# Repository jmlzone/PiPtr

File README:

This is the README for the Rasberry Pi Ham Hadio Repeater Controller
project.  The Goal of this project is to develop an inexpensive
linking repeater controller witha cost of aproximatly $100/port vs
current commerical solutions which are closer to $160/port.

This is an extensable linkable controller with both local and remote
linking.

For information on the mmra network see mmra.org
For information on this project contact jml@jmlzone.com.

For information on setting up this project on a Pi3 please see the Quickstart.txt

Most of the code will be in Python, however some of it is in C.

Eventually there will be good documeation and a bug/enhancement
tracking WIKI or some such thing.

Current state: The test repeater is stable on the air but many many
things are still to be done.

----------------------------------------------------------------------
Mailing lists for the project
  Please join one or more of the groups below.
MMRA-PiPtr-Hardware+subscribe@groups.io
MMRA-PiPtr-Software+subscribe@groups.io
MMRA-PiPtr-Documentation+subscribe@groups.io

----------------------------------------------------------------------

As you know the MMRA maintains a network of 22 repeaters.  A repeater
is basically a receiver, a transmitter and a controller
in-between. While the network generally works, there are some upgrades
we are continually working on.  One of these efforts being led by me,
James N1DDK, is developing a new repeater controller to enhance the
remote controllability, monitoring and adjusting of the
repeaters. Most of the repeater controller in use today are based on
designs over 20 years old. There have been many advances in technology
in the past 20 years. This project is bringing a more modern, more
scalable and more software based and controllable approach based on
mostly standard hardware and using popular modern methods.

 There are some guiding principles to this project:
1) No Jumpers, switches or mechanical pots that can be set incorectly at a site needing a return visit.
2) Open source -- its part of the Ham culture to experiment and share. This will also ensure longevity of the project beyond the initial developers.
3) Better ease of use than similar commercial products.
4) Scaleability and cost per port more effective than the commercial products.
5) Mostly software for simple functions like CTCSS encode / decode, DTMF encode / decode, timers, morse etc.
6) Well documented

Goals
 * Ease of use for users and control operators.
 * Web back end to view status and control linking.
 * Ability to sell hardware as a fundraiser for MMRA.

To this end I have been working mostly solo with some input from K1IW and W1BRI (and some non members) and I have a working prototype on the air on 224.080 as part of a test platform. The next goals will be to make some boards and have further testing and development.

Here is a list of some of the help that is desired:
 * Programming help in C and Python (possibly java/java script for some of the web interface)
 * Schematics design/review for the custom audio board.
 * Documentation help -- there is some basic documentation, but it would be good to have much more on both hardware, software and user guides.
 * Mechanical/sheet metal design for an enclosure, etc
 * Building help, both mechanical and building the initial boards for testing.
 * Testing help using the controller on a bench and trying things before we put them on the air.
 * On the air testing.

Want to learn more?
 There is a git-hub repository for the software, documentation and issue tracking:
https://github.com/jmlzone/PiPtr
There may be a talk about the project at Boxborough!

Even if you don't know anything about software or repeater controllers you can still help! You don't need to know anything to be a documentation volunteer!

Ready to help?
Contact James, n1ddk@mmra.org.

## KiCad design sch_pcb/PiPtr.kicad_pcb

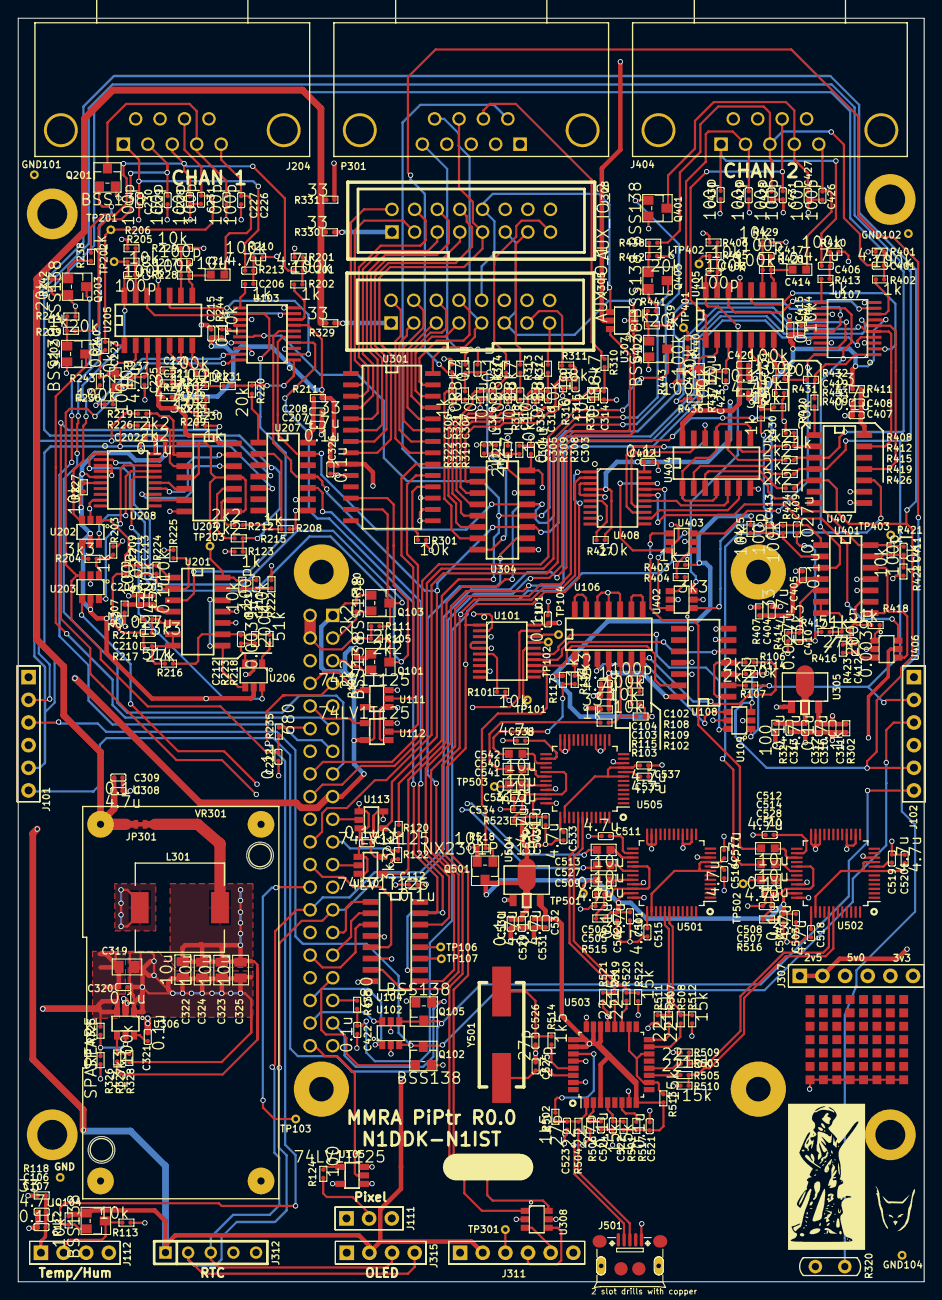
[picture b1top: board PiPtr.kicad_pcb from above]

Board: 4 copper layers, 101.6 x 141.7 mm, 388 parts (1 on the bottom side), 297 nets.

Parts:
C101, C104, C107, C111, C112, C202, C205, C207, C215, C220, C222, C303, C304, C306, C307, C309, C310, C313, C314, C315, C316, C317, C318, C320, C321, C326, C402, C405, C407, C415, C420, C422, C502, C504, C506, C508, C521, C522, C530, C531, C536, C543: 0.1u; OPL_C0402
C102, C203, C211, C213, C217, C219, C226, C227, C228, C229, C230, C231, C403, C411, C413, C417, C419, C426, C427, C428, C429, C430, C431: 100p; OPL_C0402
C103, C106, C201, C204, C206, C208, C221, C225, C305, C308, C311, C312, C401, C404, C406, C408, C421, C425, C501, C503, C505, C507, C513, C514, C515, C516, C517, C518, C519, C520, C529, C532, C533, C534, C535, C537, C538, C539: 4.7u; OPL_C0402
C209, C210, C409, C410: 0.027u; OPL_C0402
C212, C412: 0.0039u; OPL_C0402
C214, C223, C414, C423, C509, C510, C511, C512, C527, C528, C540, C541, C542: 10u; OPL_C0603
C319: 10u 25V; OPL_C0805
C322, C323, C324, C325: 10u; OPL_C0805
C523, C524, C525, C526: 27p; OPL_C0402
GND101, GND102, GND103, GND104: TESTPOINT; Wire_28AWG
J101: GLOBAL_LINK_LEFT; OPL_H6-2.54
J102: GLOBAL_LINK_RIGHT; OPL_H6-2.54
J107: RASPBERRY_PI; RaspberryPi2x20
J111: FP_PIXEL; OPL_H3-2.54
J112: AM2302; OPL_H4-2.54
J204, J404: DE9F; DE9F_Right_Angle
J305: AUX_IO_1; RibbonHeader2x8
J307: SPARE; OPL_H6-2.54
J308: AUX_IO_2; RibbonHeader2x8
J311: I2C1_5V; OPL_H6-2.54
J312: RTC; SIL-5
J315: OLED_SSD1306; OPL_H4-2.54
J501: MicroUSB; OPL_MICRO-USB5+4P-SMD-0.65-B
JP301: 5V_switcher_connect; JUMPER_2PIN_CUTTABLE
L301: 10uH; Inductor_Wurth_7447714100
LOGO301: MOUNTING_HOLE; BOBCAT_LOGO
LOGO302: MOUNTING_HOLE; mmra_logo
MTG301, MTG302, MTG303, MTG304: MOUNTING_HOLE; MTG_4_40
P301: Chassis; DE9M_Right_Angle
PROTO301: MOUNTING_HOLE; SMD_proto_area
Q101, Q102, Q103, Q104, Q105, Q201, Q202, Q203, Q401, Q402, Q403: BSS138; OPL_SOT-23
Q501: NX2301P,215; OPL_SOT-23
R101, R102, R109, R112, R113, R206, R209, R221, R222, R225, R227, R229, R233, R244, R301, R309, R315, R316, R317, R318, R319, R323, R406, R409, R421, R422, R425, R427, R429, R433, R444, R518: 10k; OPL_R0402
R103, R117, R123, R202, R203, R208, R213, R230, R238, R239, R302, R322, R402, R403, R408, R413, R430, R438, R439: 1k; OPL_R0402
R104, R105, R107, R110, R111, R114, R120, R212, R215, R219, R226, R308, R412, R415, R419, R426: 2k2; OPL_R0402
R106, R220, R231, R241, R242, R243, R420, R431, R441, R442, R443: 20k; OPL_R0402
R108, R201, R205, R210, R224, R228, R232, R236, R237, R240, R327, R401, R405, R410, R424, R428, R432, R436, R437, R440: 100k; OPL_R0402
R115, R118, R207, R211, R234, R329, R330, R331, R407, R411, R434, R515, R516, R523: 33; OPL_R0402
R116, R122, R204, R404: 3k3; OPL_R0402
R124, R324: 100; OPL_R0402
R214, R328, R414: 13k3; OPL_R0402
R216, R218, R416, R418: 51k; OPL_R0402
R217, R417: 27k; OPL_R0402
R223, R423: 200k; OPL_R0402
R235, R435: 680; OPL_R0402
R310, R311, R312, R313, R314, R321: 88k7; OPL_R0402
R320: A1050; LDR
R325, R326: SPARE; OPL_R0402
R501, R509, R510, R511, R512, R513, R517, R521, R522: 15k; OPL_R0402
R502, R514: 1k5; OPL_R0402
R503, R504, R505, R506, R507, R508, R519, R520: 22; OPL_R0402
TP101, TP102, TP103, TP104, TP106, TP107, TP201, TP202, TP203, TP301, TP401, TP402, TP403: TESTPOINT; Wire_28AWG
TP501: CH1_RIGHT; Wire_28AWG
TP502: CH2_RIGHT; Wire_28AWG
TP503: CH3_RIGHT; Wire_28AWG
U101, U208, U408: MCP23008; OPL_TSSOP20-0.65-6.5X4.4MM
U102, U307, U308: IP4234CZ6; OPL_SOT-23-6
U103, U107: MCP4351; OPL_TSSOP20-0.65-6.5X4.4MM
U104: 74HCT138; SOIC16
U105, U110, U111, U112, U113: 74LV1T125; OPL_SOT-23-5
U106, U201, U205, U401, U405: MCP6004T; SOIC14
U108, U204, U404: 74LVC4066; SOIC14
U109, U202, U203, U206, U402, U403, U406: 74LVC1G3157; OPL_SOT-23-6
U207, U407: MCP6S26; SOIC14
U301: MCP23017; SOIC28
U304: MCP3008; SOIC16
U305: MCP1703A-2502/MB; OPL_SOT-89
U306: TPS54302; OPL_SOT-23-6
U501, U502, U505: CM108B; LQFP-48_7x7mm_Pitch0.5mm
U503: TUSB2036; LQFP-32_7x7mm_Pitch0.8mm
U504: MCP1703A-3302/MB; OPL_SOT-89
VR301: VRM2596; mod20x44
Y501: 6MHz; Crystal_HC49-SD_SMD

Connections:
+2V5: C310.1, C311.1, J307.1, J307.2, R102.1, R109.1, R117.2, R123.1, R201.1, R203.1, R206.1, R208.1, R209.1, R210.1, R214.1, R222.1, R225.1, R229.1, R233.1, R243.1, R302.1, R308.1, R401.1, R403.1, R406.1, R408.1, R409.1, R410.1, R414.1, R422.1, R425.1, R429.1, R433.1, R443.1, U103.3, U103.10, U103.13, U103.18, U107.3, U107.10, U107.13, U107.18, U201.10, U207.8, U305.3, U401.10, U407.8
+3.3VP: C521.2, C531.1, C532.1, R501.2, R513.1, R517.2, U503.3, U503.8, U503.22, U503.23, U503.25, U503.26, U504.3
+3V3: J101.1, J102.1, J107.1, J107.17, J307.5, J307.6, J311.2, J312.1, J315.2, Q101.1, Q103.1, Q104.1, R104.1, R110.1, R112.1, U102.5, U111.5, U112.5, U307.5
+5V: C101.2, C111.1, C112.2, C202.2, C215.1, C303.1, C308.1, C309.1, C326.2, C402.2, C415.1, J107.2, J107.4, J111.1, J307.3, J307.4, J311.1, JP301.1, Q501.2, R101.2, R105.1, R111.1, R113.1, R115.2, R118.2, R207.2, R211.2, R227.2, R234.2, R244.1, R301.2, R320.1, R324.2, R329.2, R330.2, R331.2, R407.2, R411.2, R427.2, R434.2, R444.1, R518.2, U101.4, U101.5, U101.20, U103.7, U104.6, U104.16, U105.5, U107.7, U109.5, U110.5, U113.5, U202.5, U203.5, U206.5, U208.5, U208.20, U301.9, U301.17, U304.16, U308.5, U402.5, U403.5, U406.5, U408.4, U408.20, VR301.3
+5VP: C501.1, C502.1, C503.1, C504.1, C529.1, C530.1, C539.1, C543.1, Q501.3, R515.2, R516.2, R523.2, U501.35, U502.35, U504.2, U504.4, U505.35
+12V: C319.1, C320.1, P301.5, R321.1, R325.1, U306.3, VR301.1
/CE0_33: J107.24, U104.5
/CH1/CTCSS_FROM_RADIO: R203.2, R204.1, U203.1
/CH1/CTCSS_FROM_RX_AUDIO: C209.2, C213.1, R224.1, U201.1, U202.1
/CH1/PORT_DET_EN: U203.6, U208.18
/CH1/PTT: C227.1, J204.4, Q201.3
/CH1/RX_AUDIO: C206.2, C230.1, J204.1
/CH1/RX_BUS1_EN: U204.12, U208.13
/CH1/RX_BUS2_EN: U204.13, U208.14
/CH1/RX_BUS3_EN: U204.5, U208.15
/CH1/RX_COR: C229.1, J204.2, R239.1
/CH1/RX_CTCSS: C201.2, C228.1, J204.3, R238.2
/CH1/RX_DEEMP_EN: U206.6, U208.16
/CH1/RX_DESC_EN: U202.6, U208.17
/CH1/RX_LOCAL_EN: U204.6, U208.12
/CH1/TONE_FROM_PI: C222.1, R235.1, U103.20, U203.3
/CH1/TX_AUDIO: C214.1, C226.1, J204.5
/CH1/TX_CTCSS: C231.1, J204.8, R240.1, TP201.1, U205.1
/CH1/VDDA_1: C204.1, C205.1, R207.1, U201.4
/CH1/VDDA_2: C220.1, C221.1, R234.1, U204.14, U205.4
/CH1/VDDA_3: C207.1, C208.1, R211.1, U207.14
/CH2/CTCSS_FROM_RADIO: R403.2, R404.1, U403.1
/CH2/CTCSS_FROM_RX_AUDIO: C409.2, C413.1, R424.1, U401.1, U402.1
/CH2/PORT_DET_EN: U403.6, U408.18
/CH2/PTT: C427.1, J404.4, Q401.3
/CH2/RX_AUDIO: C406.2, C430.1, J404.1
/CH2/RX_BUS1_EN: U404.12, U408.13
/CH2/RX_BUS2_EN: U404.13, U408.14
/CH2/RX_BUS3_EN: U404.5, U408.15
/CH2/RX_COR: C429.1, J404.2, R439.1
/CH2/RX_CTCSS: C401.2, C428.1, J404.3, R438.2
/CH2/RX_DEEMP_EN: U406.6, U408.16
/CH2/RX_DESC_EN: U402.6, U408.17
/CH2/RX_LOCAL_EN: U404.6, U408.12
/CH2/TONE_FROM_PI: C422.1, R435.1, U107.20, U403.3
/CH2/TX_AUDIO: C414.1, C426.1, J404.5
/CH2/TX_CTCSS: C431.1, J404.8, R440.1, TP401.1, U405.1
/CH2/VDDA_1: C404.1, C405.1, R407.1, U401.4
/CH2/VDDA_2: C420.1, C421.1, R434.1, U404.14, U405.4
/CH2/VDDA_3: C407.1, C408.1, R411.1, U407.14
/COR1: J107.11, Q202.3
/COR2: J107.16, Q402.3
/DHT_5: J112.2, Q104.3, R113.2
/DHT_33: J107.7, Q104.2, R112.2
/LINK1C: J101.3, J102.3, Q102.3, U102.3
/LINK1O: J107.33, Q102.1
/LINK2C: J101.6, J102.6, Q105.3, U102.4
/LINK2O: J107.37, Q105.1
/MISO_33: J107.21, R120.2, R122.1
/MOSI_33: J107.19, U113.2
/PIXEL_33: J107.40, U105.2
/PTT1D: J107.15, Q201.1
/PTT2D: J107.22, Q401.1
/PWM0: J107.12, R235.2
/PWM1: J107.35, R435.2
/SC3_LINK1: U101.13, U108.13
/SC3_LINK2: U101.14, U108.5
/SC3_LINK_SEL: U101.15, U109.6
/SCL0_33: J107.28, J312.3, J315.3, U307.1
/SCL1_33: J107.5, Q101.2, R104.2
/SCLK_33: J107.23, U110.2
/SC_ENA: Q501.1, R518.1, U101.12
/SDA0_33: J107.27, J312.2, J315.4, U307.6
/SDA1_33: J107.3, Q103.2, R110.2
/SELA_33: J107.29, U104.1
/SELB_33: J107.31, U104.2
/SELC_33: J107.32, U104.3
/Spares, GPIO, and ADC/ADC0: P301.6, U304.1
/Spares, GPIO, and ADC/ADC1: P301.7, R310.1
/Spares, GPIO, and ADC/ADC2: J305.13, R311.1
/Spares, GPIO, and ADC/ADC3: J305.15, R312.1
/Spares, GPIO, and ADC/ADC4: J308.13, R313.1
/Spares, GPIO, and ADC/ADC5: J308.15, R314.1
/Spares, GPIO, and ADC/ADC_LIGHT: C306.1, R320.2, R322.1, U304.7
/Spares, GPIO, and ADC/ADC_VIN: C307.1, R321.2, R323.1, U304.8
/Spares, GPIO, and ADC/GPA0: J305.2, U301.21
/Spares, GPIO, and ADC/GPA1: J305.3, U301.22
/Spares, GPIO, and ADC/GPA2: J305.4, U301.23
/Spares, GPIO, and ADC/GPA3: J305.5, U301.24
/Spares, GPIO, and ADC/GPA4: J305.6, U301.25
/Spares, GPIO, and ADC/GPA5: J305.7, U301.26
/Spares, GPIO, and ADC/GPA6: J305.8, U301.27
/Spares, GPIO, and ADC/GPA7: J305.9, P301.9, U301.28
/Spares, GPIO, and ADC/GPB0: J308.2, U301.1
/Spares, GPIO, and ADC/GPB1: J308.3, U301.2
/Spares, GPIO, and ADC/GPB2: J308.4, U301.3
/Spares, GPIO, and ADC/GPB3: J308.5, U301.4
/Spares, GPIO, and ADC/GPB4: J308.6, U301.5
/Spares, GPIO, and ADC/GPB5: J308.7, U301.6
/Spares, GPIO, and ADC/GPB6: J308.8, U301.7
/Spares, GPIO, and ADC/GPB7: J308.9, P301.8, U301.8
/Spares, GPIO, and ADC/SCL0_OUT: J305.11, J308.11, U307.3
/Spares, GPIO, and ADC/SDA0_OUT: J305.10, J308.10, U307.4
/UINTA_5: U111.2, U301.20
/UINTA_33: J107.8, U111.4
/UINTB_5: U112.2, U301.19
/UINTB_33: J107.10, U112.4
/VDDA_3: C103.1, C104.1, R115.1, U106.4, U108.14
/soundcard/D_N: J501.2, R506.2
/soundcard/D_P: J501.3, R504.2
/soundcard/FROM_SND1: C527.1, R230.2
/soundcard/FROM_SND2: C528.1, R430.2
/soundcard/FROM_SND3: C540.1, R103.2
/soundcard/TO_SND1: C511.1, U203.4
/soundcard/TO_SND2: C512.1, U403.4
/soundcard/TO_SND3: C542.1, R116.1, R117.1
/soundcard/U1N: R508.1, R512.2, U501.42
/soundcard/U1P: R507.1, R511.2, U501.41
/soundcard/U2N: R505.1, R510.2, U502.42
/soundcard/U2P: R503.1, R509.2, U502.41
/soundcard/U3N: R520.1, R522.2, U505.42
/soundcard/U3P: R519.1, R521.2, U505.41
/~ADC_CS: U104.7, U304.10
/~CTCSS1: J107.13, Q203.3
/~CTCSS2: J107.18, Q403.3
/~PGA1_CS: U104.10, U207.10
/~PGA2_CS: U104.9, U407.10
/~R03CS: U103.4, U104.15
/~R47CS: U104.14, U107.4
/~UINT_ENA: U101.19, U111.1, U112.1
GND: C101.1, C103.2, C104.2, C106.2, C107.2, C111.2, C112.1, C202.1, C204.2, C205.2, C207.2, C208.2, C215.2, C220.2, C221.2, C222.2, C225.2, C226.2, C227.2, C228.2, C229.2, C230.2, C231.2, C303.2, C304.2, C305.2, C306.2, C307.2, C308.2, C309.2, C310.2, C311.2, C312.2, C313.2, C314.2, C315.2, C316.2, C317.2, C318.2, C319.2, C320.2, C322.2, C323.2, C324.2, C325.2, C326.1, C402.1, C404.2, C405.2, C407.2, C408.2, C415.2, C420.2, C421.2, C422.2, C425.2, C426.2, C427.2, C428.2, C429.2, C430.2, C431.2, C501.2, C502.2, C503.2, C504.2, C505.2, C506.2, C507.2, C508.2, C513.2, C514.2, C515.2, C516.2, C517.2, C518.2, C519.2, C520.2, C521.1, C522.2, C523.2, C524.2, C525.2, C526.2, C529.2, C530.2, C531.2, C532.2, C533.2, C534.2, C535.2, C536.2, C537.2, C538.2, C539.2, C543.2, GND101.1, GND102.1, GND103.1, GND104.1, J101.4, J102.4, J107.6, J107.9, J107.14, J107.20, J107.25, J107.30, J107.34, J107.39, J111.3, J112.4, J204.6, J204.7, J204.9, J305.12, J305.14, J308.12, J308.14, J311.6, J312.5, J315.1, J404.6, J404.7, J404.9, J501.5, P301.2, P301.3, P301.4, PROTO301.1, Q102.2, Q105.2, Q201.2, Q202.2, Q203.2, Q401.2, Q402.2, Q403.2, R122.2, R241.2, R242.2, R302.2, R309.2, R315.2, R316.2, R317.2, R318.2, R319.2, R322.2, R323.2, R326.2, R328.2, R441.2, R442.2, R509.1, R510.1, R511.1, R512.1, R521.1, R522.1, U101.3, U101.9, U102.2, U103.17, U104.4, U104.8, U105.1, U105.3, U106.10, U106.11, U106.12, U107.17, U108.6, U108.7, U108.8, U108.11, U108.12, U109.2, U110.1, U110.3, U111.3, U112.3, U113.1, U113.3, U201.11, U202.2, U203.2, U204.7, U205.11, U206.2, U207.9, U208.3, U208.4, U208.9, U301.10, U301.15, U301.16, U304.9, U304.14, U305.1, U306.1, U307.2, U308.2, U401.11, U402.2, U403.2, U404.7, U405.11, U406.2, U407.9, U408.3, U408.5, U408.9, U501.10, U501.14, U501.16, U501.22, U501.23, U501.24, U501.33, U501.36, U502.10, U502.14, U502.16, U502.22, U502.23, U502.24, U502.33, U502.36, U503.7, U503.21, U503.24, U503.28, U503.31, U504.1, U505.10, U505.14, U505.16, U505.22, U505.23, U505.24, U505.33, U505.36, VR301.2, VR301.4
LINK1_AUD: J101.2, J102.2, R107.1, R219.1, R419.1, U109.1, U207.4, U407.4
LINK2_AUD: J101.5, J102.5, R114.1, R226.1, R426.1, U109.3, U207.5, U407.5
LOCAL_LINK_AUD: R123.2, R215.1, R415.1, U207.3, U407.3
MISO_5: R120.1, U103.16, U107.16, U304.12
MOSI_5: U103.6, U107.6, U113.4, U207.11, U304.11, U407.11
unnamed: C102.1, R106.2, R108.1, U106.7
unnamed: C102.2, R108.2, R109.2, U106.6
unnamed: C106.1, C107.1, J112.1, R118.1
unnamed: C201.1, R201.2, R202.2
unnamed: C203.1, R205.1, TP202.1, U202.3, U205.14
unnamed: C203.2, R205.2, R206.2, U205.13
unnamed: C206.1, R210.2, R213.2
unnamed: C209.1, C210.2, R217.1
unnamed: C210.1, R214.2, U201.5
unnamed: C211.1, R221.1, TP203.1, U201.14, U204.1, U204.4, U204.8, U204.11
unnamed: C211.2, R221.2, R222.2, U201.13
unnamed: C212.1, R223.1, U206.3
unnamed: C212.2, R216.1, R218.2, R223.2, U201.9
unnamed: C213.2, R224.2, R225.2, U201.2
unnamed: C214.2, C217.1, R228.1, U205.8
unnamed: C217.2, R228.2, R229.2, U205.9
unnamed: C219.1, R231.2, R232.1, U205.7
unnamed: C219.2, R232.2, R233.2, U205.6
unnamed: C223.1, R236.1, R237.2
unnamed: C223.2, R240.2, R243.2, U205.2
unnamed: C225.1, R237.1, U205.3
unnamed: C304.1, C305.1, R308.2, R309.1, U304.15
unnamed: C312.1, C313.1, R324.1, U305.2, U305.4
unnamed: C314.1, R310.2, R315.1, U304.2
unnamed: C315.1, R311.2, R316.1, U304.3
unnamed: C316.1, R312.2, R317.1, U304.4
unnamed: C317.1, R313.2, R318.1, U304.5
unnamed: C318.1, R314.2, R319.1, U304.6
unnamed: C321.1, U306.6
unnamed: C321.2, L301.2, U306.2
unnamed: C322.1, C323.1, C324.1, C325.1, JP301.2, L301.1, R327.1
unnamed: C401.1, R401.2, R402.2
unnamed: C403.1, R405.1, TP402.1, U402.3, U405.14
unnamed: C403.2, R405.2, R406.2, U405.13
unnamed: C406.1, R410.2, R413.2
unnamed: C409.1, C410.2, R417.1
unnamed: C410.1, R414.2, U401.5
unnamed: C411.1, R421.1, TP403.1, U401.14, U404.1, U404.4, U404.8, U404.11
unnamed: C411.2, R421.2, R422.2, U401.13
unnamed: C412.1, R423.1, U406.3
unnamed: C412.2, R416.1, R418.2, R423.2, U401.9
unnamed: C413.2, R424.2, R425.2, U401.2
unnamed: C414.2, C417.1, R428.1, U405.8
unnamed: C417.2, R428.2, R429.2, U405.9
unnamed: C419.1, R431.2, R432.1, U405.7
unnamed: C419.2, R432.2, R433.2, U405.6
unnamed: C423.1, R436.1, R437.2
unnamed: C423.2, R440.2, R443.2, U405.2
unnamed: C425.1, R437.1, U405.3
unnamed: C505.1, C506.1, R515.1, U501.29, U501.34
unnamed: C507.1, C508.1, R516.1, U502.29, U502.34
unnamed: C509.1, TP501.1
unnamed: C509.2, U501.32
unnamed: C510.1, TP502.1
unnamed: C510.2, U502.32
unnamed: C511.2, U501.27
unnamed: C512.2, U502.27
unnamed: C513.1, U501.26
unnamed: C514.1, U502.26
unnamed: C515.1, U501.37
unnamed: C516.1, U501.8
unnamed: C517.1, U501.7, U501.9, U501.38
unnamed: C518.1, U502.37
unnamed: C519.1, U502.8
unnamed: C520.1, U502.7, U502.9, U502.38
unnamed: C522.1, R501.1, U503.4
unnamed: C523.1, R502.2, R504.1, U503.1
unnamed: C524.1, R506.1, U503.2
unnamed: C525.1, U503.30, Y501.1
unnamed: C526.1, R514.2, Y501.2
unnamed: C527.2, U501.30
unnamed: C528.2, U502.30
unnamed: C533.1, U505.37
unnamed: C534.1, C536.1, R523.1, U505.29, U505.34
unnamed: C535.1, U505.8
unnamed: C537.1, U505.7, U505.9, U505.38
unnamed: C538.1, U505.26
unnamed: C540.2, U505.30
unnamed: C541.1, TP503.1
unnamed: C541.2, U505.32
unnamed: C542.2, U505.27
unnamed: J107.26, TP103.1
unnamed: J107.36, U102.1
unnamed: J107.38, U102.6
unnamed: J111.2, R124.1
unnamed: J305.1, R329.1
unnamed: J308.1, R330.1
unnamed: J311.3, TP301.1
unnamed: J311.4, U308.4
unnamed: J311.5, U308.3
unnamed: P301.1, R331.1
unnamed: Q202.1, R239.2, R241.1
unnamed: Q203.1, R238.1, R242.1
unnamed: Q402.1, R439.2, R441.1
unnamed: Q403.1, R438.1, R442.1
unnamed: R101.1, U101.6
unnamed: R102.2, R103.1, U106.5
unnamed: R106.1, U108.1, U108.4
unnamed: R107.2, U108.2
unnamed: R114.2, U108.3
unnamed: R116.2, U106.1, U106.2
unnamed: R124.2, U105.4
unnamed: R202.1, U103.8
unnamed: R204.2, U202.4
unnamed: R208.2, R212.1, U207.2
unnamed: R209.2, R230.1, U205.5
unnamed: R212.2, U204.9
unnamed: R213.1, U103.11
unnamed: R215.2, U204.10
unnamed: R216.2, R217.2, U201.6, U201.7
unnamed: R218.1, U206.1
unnamed: R219.2, U204.2
unnamed: R220.1, R231.1, U103.1
unnamed: R220.2, U207.1
unnamed: R226.2, U204.3
unnamed: R227.1, U208.6
unnamed: R236.2, U103.19
unnamed: R244.2, U103.15
unnamed: R301.1, U301.18
unnamed: R325.2, R326.1, U306.5
unnamed: R327.2, R328.1, U306.4
unnamed: R402.1, U107.8
unnamed: R404.2, U402.4
unnamed: R408.2, R412.1, U407.2
unnamed: R409.2, R430.1, U405.5
unnamed: R412.2, U404.9
unnamed: R413.1, U107.11
unnamed: R415.2, U404.10
unnamed: R416.2, R417.2, U401.6, U401.7
unnamed: R418.1, U406.1
unnamed: R419.2, U404.2
unnamed: R420.1, R431.1, U107.1
unnamed: R420.2, U407.1
unnamed: R426.2, U404.3
unnamed: R427.1, U408.6
unnamed: R436.2, U107.19
unnamed: R444.2, U107.15
unnamed: R502.1, U503.27
unnamed: R503.2, U503.12
unnamed: R505.2, U503.11
unnamed: R507.2, U503.16
unnamed: R508.2, U503.15
unnamed: R513.2, U503.10, U503.14, U503.18
unnamed: R514.1, U503.29
unnamed: R517.1, U503.6
unnamed: R519.2, U503.20
unnamed: R520.2, U503.19
unnamed: TP101.1, U101.16
unnamed: TP102.1, U101.17
unnamed: TP104.1, U101.18
unnamed: TP106.1, U104.12
unnamed: TP107.1, U104.11
unnamed: U103.2, U205.10
unnamed: U103.9, U205.12
unnamed: U103.12, U201.3
unnamed: U106.3, U109.4
unnamed: U106.8, U106.9
unnamed: U106.13, U106.14
unnamed: U107.2, U405.10
unnamed: U107.9, U405.12
unnamed: U107.12, U401.3
unnamed: U201.8, U201.12, U206.4
unnamed: U401.8, U401.12, U406.4
SCL1_5: Q101.3, R105.2, U101.1, U208.1, U301.12, U308.6, U408.1
SCLK_5: U103.5, U107.5, U110.4, U207.13, U304.13, U407.13
SDA1_5: Q103.3, R111.2, U101.2, U208.2, U301.13, U308.1, U408.2

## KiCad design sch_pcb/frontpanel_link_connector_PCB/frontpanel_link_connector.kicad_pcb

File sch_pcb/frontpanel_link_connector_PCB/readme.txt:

This directory contains the schematic and PCB for the front panel connector board.  This will be used at the leftmost and rightmost 
boards in a rack chassis to allow interconnecting between chasses

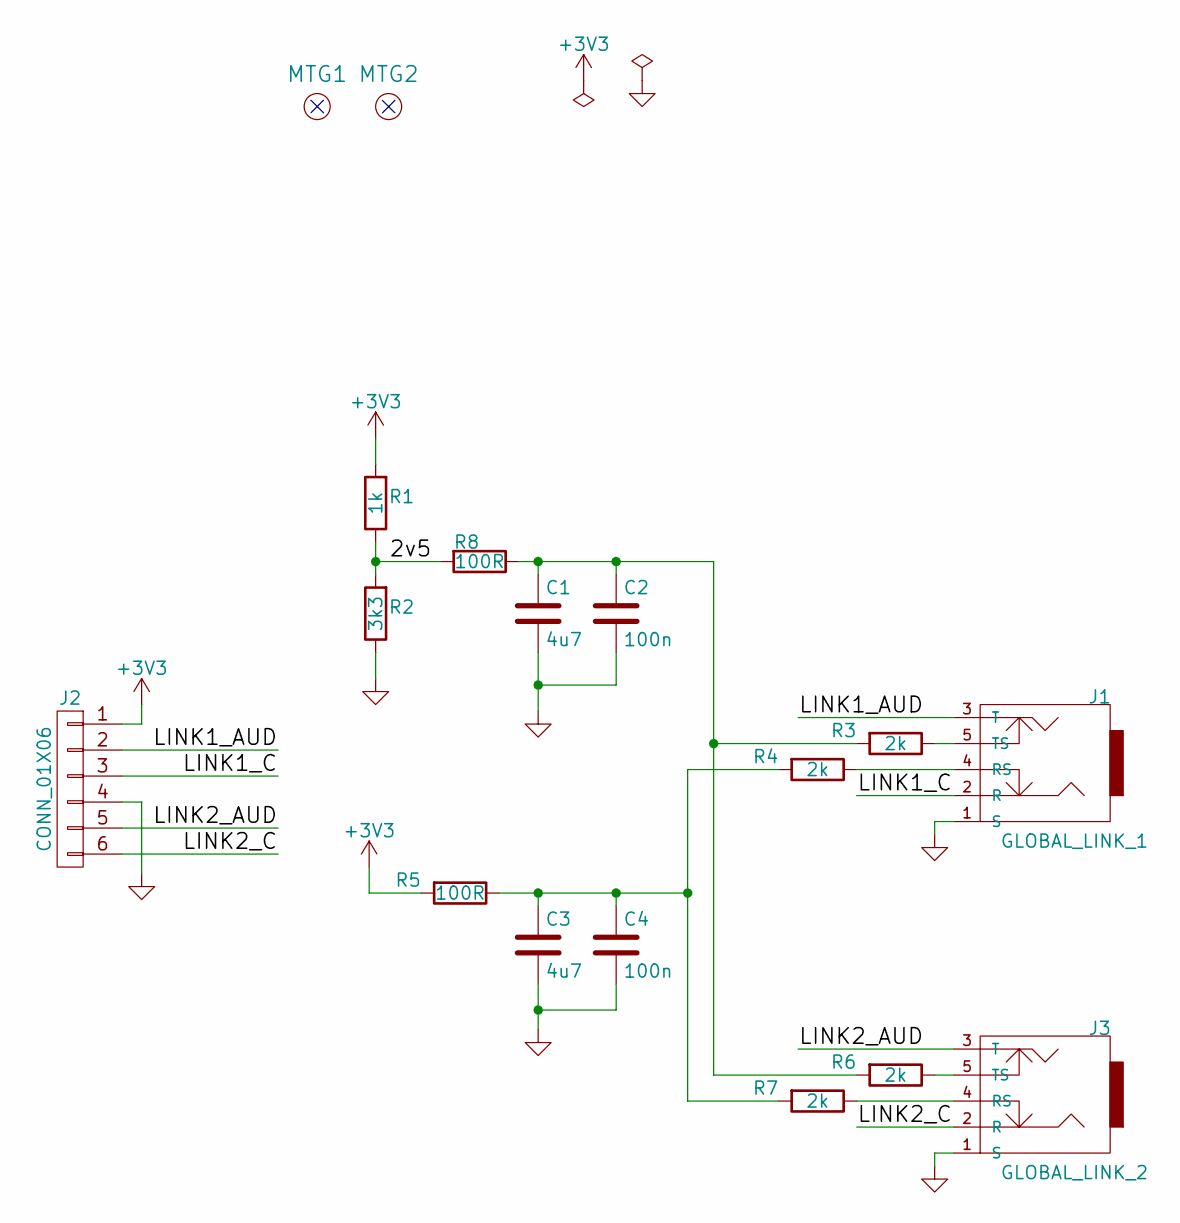
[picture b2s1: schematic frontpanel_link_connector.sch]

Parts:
C1, C3: 4u7; smd0603
C2, C4: 100n; smd0603
J1: GLOBAL_LINK_1; TRS3.5_5
J2: CONN_01X06; Molex_22-27-2061_100mil_6pin_verical
J3: GLOBAL_LINK_2; TRS3.5_5
MTG1, MTG2: MOUNTING_HOLE; MTG_4_40
R1: 1k; smd0603
R2: 3k3; smd0603
R3, R4, R6, R7: 2k; smd0603
R5, R8: 100R; smd0603

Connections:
+3V3: J2.1, R1.2, R5.2
/2v5: R1.1, R2.2, R8.2
/LINK1_AUD: J1.3 (T), J2.2
/LINK1_C: J1.2 (R), J2.3
/LINK2_AUD: J2.5, J3.3 (T)
/LINK2_C: J2.6, J3.2 (R)
GND: C1.2, C2.2, C3.2, C4.2, J1.1 (S), J2.4, J3.1 (S), R2.1
unnamed: C1.1, C2.1, R3.2, R6.2, R8.1
unnamed: C3.1, C4.1, R4.2, R5.1, R7.2
unnamed: J1.4 (RS), R4.1
unnamed: J1.5 (TS), R3.1
unnamed: J3.4 (RS), R7.1
unnamed: J3.5 (TS), R6.1

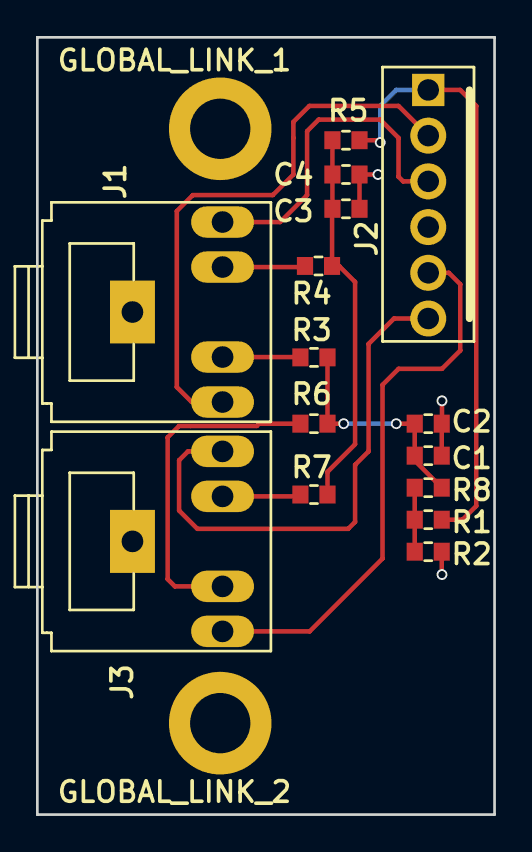
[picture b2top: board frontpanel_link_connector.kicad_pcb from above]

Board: 2 copper layers, 25.4 x 43.2 mm, 17 parts (0 on the bottom side), 13 nets.

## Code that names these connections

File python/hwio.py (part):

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
""" User IO pin naames
"""
GPA0 = 0
GPA1 = 1
GPA2 = 2
GPA3 = 3
GPA4 = 4
GPA5 = 5
GPA6 = 6
GPA7 = 7
GPB0 = 8
GPB1 = 9
GPB2 = 10
GPB3 = 11
GPB4 = 12
GPB5 = 13
GPB6 = 14
GPB7 = 15
# HWIO directions
INPUT = 1
OUTPUT = 0
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""" Link related pins
"""
LINK1I = 36
LINK1O = 33
LINK2I = 40
LINK2O = 37

class hwio :
    def __init__ (self,top) :
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        GPIO.setmode(GPIO.BOARD)
        GPIO.setup(self.selPins, GPIO.OUT)
        GPIO.output(self.selPins, GPIO.LOW)
        GPIO.setup([LINK1O,LINK2O], GPIO.OUT) 
        GPIO.setup([LINK1I,LINK2I], GPIO.IN)
        GPIO.output([LINK1O,LINK2O], GPIO.LOW)
        self.vals = [150,2,50,20,0,0,0,0]
        self.tcon = [15,15,15,15,15,15,15,15]
        self.gain = [ [6,6,6,6], [6,6,6,6] ]
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            oldVotes = self.elink1Votes
            self.elink1Votes = oldVotes | (1<<port)
            if(oldVotes==0) :
                GPIO.output(LINK1O,GPIO.HIGH)
        elif(link==3) :
            oldVotes = self.elink2Votes
            self.elink2Votes = oldVotes | (1<<port)
            if(oldVotes==0) :
                GPIO.output(LINK2O,GPIO.HIGH)
        else:
            pass
    def linkVoteClr(self, port, link) :
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        if(link==2) :
            self.elink1Votes = self.elink1Votes &  ~(1<<port)
            if(self.elink1Votes==0) :
                GPIO.output(LINK1O,GPIO.LOW)
        elif(link==3) :
            self.elink2Votes = self.elink2Votes & ~(1<<port)
            if(self.elink2Votes==0) :
                GPIO.output(LINK2O,GPIO.LOW)
        else:
            pass
    
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        for n in range(plen) :
            pin = pins[n]
            pu = pull_up_down[n]
            if(pin >=GPA0 and pin <=GPA7 ) :
                self.iodirA = self.updateMask(self.iodirA,pin,direction)
                self.gppuA = self.updateMask(self.gppuA,pin,pu)
                if(initial is not None) :
                    self.ovalA =  self.updateMask(self.ovalA,pin,initial[n])
                updateA = True
            elif(pin >=GPB0 and pin <=GPB7 ) :
                pin = pin - GPB0
                self.iodirB = self.updateMask(self.iodirB,pin,direction)
                self.gppuB = self.updateMask(self.gppuB,pin,pu)
                if(initial is not None) :
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        updateA = False
        updateB = False
        for pin in pinlist :
            if(pin >=GPA0 and pin <=GPA7 ) :
                updateA = True
            elif(pin >=GPB0 and pin <=GPB7 ) :
                pin = pin - GPB0
                updateB = True
            else:
                print("Ilegal HWIO pin for input %d" % pin)
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            return(rv)

    def add_event_detect(self,pin,intEdge,callback=None) :
        if(pin >=GPA0 and pin <=GPA7 ) :
            self.intenA = self.getBit(self.intenA,1,pin)
            self.userfuncs[pin] = callback
            self.intEdge[pin] = intEdge
            self.i2cSafeWrite(GPIOEX4,GPINTENA,self.intenA)
        elif(pin >=GPB0 and pin <=GPB7 ) :
            self.intenB = self.getBit(self.intenB,1,pin-8)
            self.userfuncs[pin] = callback
            self.intEdge[pin] = intEdge
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            

    def remove_event_detect(self,pin) :
        if(pin >=GPA0 and pin <=GPA7 ) :
            self.intenA = self.getBit(self.intenA,0,pin)
            self.userfuncs[pin] = None
            self.i2cSafeWrite(GPIOEX4,GPINTENA,self.intenA)
        elif(pin >=GPB0 and pin <=GPB7 ) :
            self.intenB = self.getBit(self.intenB,0,pin-8)
            self.userfuncs[pin] = None
            self.i2cSafeWrite(GPIOEX4,GPINTENB,self.intenB)
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
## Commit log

2017-01-19 added Makefile
2017-01-24 Added a few clarifing words
2017-03-14 Basic command testing added and tested.
2017-03-16 deglitching dtmf decode and tail debugging
2017-03-25 now with tout generator and minor bug fixes.
2017-03-25 enabled tail as beep or morse
2017-04-01 setting up new structure with xml io
2017-04-02 work in progress
2017-04-04 basic canvas for test repeater controls
2017-04-07 organization of initial state machine and addition of base gui. Not runable yet
2017-04-07 timers should not start by default, wait until needed
2017-04-08 some debug
2017-04-08 added more logging and more competion of FSM
2017-04-09 added soft ctcss tone lables
2017-04-09 more debugging
2017-04-10 figured out and debugged time out deadlock
2017-04-10 basic working timer ID timers and commands Yeah we have an alpha level
2017-04-11 turn down some debug messages, correct a typo in polite Id
2017-04-15 added some doc, more cleanup of main code
2017-04-21 split rx and rpt state machines
2017-04-24 Some documentation and state machine cleanup. Adding i2c control for extra gpio
2017-04-26 more i2c setup
2017-04-26 basic debug
2017-04-26 minor tweaks to run on test hardware
2017-04-29 change print to work on both 2.7 and 3.0
2017-04-29 adding host sim basic infastructure
2017-04-29 adding a picture of flow as png
2017-04-29 change the name of png
2017-04-29 dummy multimon object for hostsim
2017-05-01 initial web api
2017-05-01 initial srv interface backend for web based gui
2017-05-14 working testbed in python3 on Pi
2017-05-14 some python 3 notes
2017-06-07 added state call back block and gui indirection
2017-06-07 debugged global state with callbacks
2017-06-11 link 1 linking and some linking infrastructure added sending to test platform for debug
2017-06-11 debug initial linking and syntax errors
2017-06-12 added some notes about pcb vendor sites
2017-06-15 added hardware front panel using neopixels
2017-06-15 debug
2017-06-16 added colorby name
2017-06-16 correct syntax
2017-06-20 add delay between calls to update to collect calls on their own thread
2017-06-21 cleanup, disconnected leds
2017-06-24 figured out rx fsm hang
2017-06-28 set up command socket port
2017-06-29 tt commands from telnet port working
2017-06-29 allow more connections
2017-06-29 made hierarchical ditcionarys work
2017-06-29 added help request
2017-06-29 cleaned up garbacge charagters
2017-06-29 style, big cleanup
2017-06-30 added socket python back door
2017-06-30 back door debug port workable
2017-07-01 protect i2c/smbus calls to allow runnining without hardware
2017-07-01 added notes on additional installs needed and made sure it does not exit without a gui
2017-07-03 commend line updates
2017-07-04 debug socket connnections and re-connecting
2017-07-04 Add files via upload
    Initial upload of schematic and (barely started) PCB layout
2017-07-06 redraw 4 Rs
2017-07-06 Updates based on emails
    Disconnect SDO on PGAs
    Add mounting holes
    More placement on PCB - for now, delete all 4xx sheet footprints. Once channel 1 is placed, it will get copied to make channel 2.
2017-07-06 gui stup for tune up of first 2 ports
2017-07-06 minor cleanup
2017-07-07 start to stage for last slider.
2017-07-07 added slider E
2017-07-07 correct rE callbacks
2017-07-07 Add files via upload
    Fix missing pin numbers on opamps
    Change two 4.7uF caps in parallel to 10uF/0805. This will save 6 caps and will handle capacitance loss due to DC bias better
    Change 2 22uF caps to 4 10uF caps to get rid of an extra BOM line item
    More work on placement. The channel now fits in the space allocated to it.
    Connectors need to be revisited - GPIO and soundcard
2017-07-08 add checkboxes and control for analog switches
2017-07-08 correct muting selection
2017-07-09 Add files via upload
    Changed user_adc connector to 2x7 (14-pin is a lot more common than 12-pin)
    Changed user_gpio connector to 2 2x8 connectors. 1x20 takes too much linear space
    First pass layout on the two audio channels. Right now, board is 4-layer, 100x150mm. May be able to knock down the 150mm dimension
    The link and soundcard connectors fit in a row across the front edge.
2017-07-10 Add files via upload
    Reversed ends on all pots so up increases level
    Added outline and mounting holes to RasPi footprint so we can see how big it really is
    Moved parts away from one of the RasPi mounting holes so we can use all 4 of them
    More routing - finished user GPIO and ADC, SPI chipselect decoder
    Still to do: level shifters, RasPi connections and spares
2017-07-12 added some notes and pictures
2017-07-18 Add files via upload
    Change link connectors to use a daughterboard for the off-rack links and 100mil headers for between-board links
2017-07-27 Add soundcard schematic
2017-07-27 Add PCB models
2017-07-29 Update to soundcard
    Split AVdd and DVdd
    Add caps and testpoints for right outputs
    Move active outputs to left channel
2017-07-30 Update from latest round of emails
    Change connectors - use correct footprint for DE9F. Add chassis connector as DE9M, AUX_IO connectors as 116-pin ribbon, expected to transition to DA15 with a cable.
    Remove screw terminals for 12V input as it now comes in on chassis connector
    Remove third EEPOT package
    Move stuff off PCB in preparation to incorporate all the schematic updates.
2017-08-06 Add files via upload
    Some new models; not all of which are used here anymore
2017-08-06 Add files via upload
    Just realized these never got committed...
2017-08-06 Delete DE15HD_M_Right_Angle_HD15_plug.kicad_mod
    Committed to wrong place; moved to lib.pretty
2017-08-06 Delete DE9F_Right_Angle.kicad_mod
    Committed to wrong place; moved to lib.pretty
2017-08-06 Delete DE9M_Right_Angle.kicad_mod
    Committed to wrong place; moved to lib.pretty
2017-08-06 Delete Diode_SMB.kicad_mod
    Committed to wrong place; moved to lib.pretty
2017-08-06 Add files via upload
    More routing of the PCB.... Slowly getting there.
2017-08-08 Add files via upload
    Remove OLED connector
    Remove extra bypass cap from third EEPOT
    More routing - got the soundcards and usb hub done. Only remaining big section is the DC-DC. Still a bit of pain-in-the-tuchas traces that need to sneak across the board...
2017-08-10 Add files via upload
    Fix sheet ordering in schematic
    Finish routing (except USB connector...)
    Still to do: USB connector, cleanup PCB, fix refdes positions
2017-08-11 Add files via upload
    Add USB connector. Pull back corner of board for it so the main board connector is around the same depth as the one on the Pi
    Finish moving all refdes to avoid pads, other silk, and vias
    Some routing cleanup
2017-08-12 add file path searching to top class and use it for command.pu and config.xlm
2017-08-12 fix up file path searching in main and radioport
2017-08-12 more path debug
2017-08-13 Flip pi
    Whoops. For all this time, the pi footprint was backwards, as if this board was a hat mounting on top of the pi. Flip it so the pi mounts face down on this board. This will put the network and usb co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
2017-08-13 Add MMRA logo
2017-08-13 Silk cleanup
2017-08-20 screenshot for presentation
2017-08-21 Add files via upload
    Add a PMOS switch to allow turning on the soundcard section (hub and 2 soundcard chips) after the Pi has booted. For some reason, doing so before the desktop loads causes it to hang..
    Change gain resistors in opamp stages to move the sweet spot closer to the center of the digital pots to allow for more adjustment range
2017-08-23 clean up debug messages and debug soft debug
2017-08-29 Add prototype area and soic-a8 footprints
2017-08-29 Update board with third soundcard
2017-09-03 modified GUI to add alsa Mixer also
2017-09-03 added bus support to ReadAll
2017-09-04 Add minimum load on 2v5 regulator. Update gain to soundcard 1 and 2
2017-09-07 BOM scrub
2017-09-13 Move link connector close to edge to allow using jumpers to connect boards
2017-09-20 Change 33pf to 100pf. Change 2k and 2200 to 2k2. Change I2C addresses for MCP23008. Nudge link connectors
2017-09-20 Change 90k to 88k7 and 50k to 51k
2017-09-25 Add files via upload
    Fix i2c addressing
    Change footprint for LDR
    Move connectors for temp/hum sensor and rtc so they won't hit the Pi
2017-09-25 Add LDR footprint
2017-09-29 Add Digikey part # to all parts. Fix unconnected nets
2017-10-06 intital hardware changes for new schematic and user IO setup
2017-10-07 add interupt direction still need to code user interupts
2017-10-09 add pullup and initial to setup
2017-10-13 command debugging
2017-10-13 add userio commands
2017-10-14 debug new commands
2017-10-15 more command mode additions
2017-10-16 some pixel debug, still hangs in render
2017-10-25 Add SeeedStudio footprints
2017-10-25 Switch to 0402 parts and SeeedStudio footprints
    Silk screen is still being updated. BOM needs to be updated as well
2017-10-27 add some more utility routines
2017-10-30 initial PCB order at seeed
2017-11-04 debug some utility commands
2017-11-04 Version with updated silkscreen
2017-11-07 typo
2017-11-07 version for initial fab
2017-11-07 add tt test functions
2017-11-07 debug towards HWIO interupts
2017-11-09 add hwio interupts
2017-11-09 interupt debug
2017-11-10 interrupt and hwio debug
2017-11-10 debug interruts
2017-12-16 debug gui
2017-12-17 working pwm functions
2017-12-17 added Make for gpio_alt
2017-12-17 mostly through port detection development
2017-12-18 stand alone port detection working
2017-12-18 integrated port detection into hwio init_all and added ipPort stub
2017-12-19 debugged port detection
2017-12-20 port detection and TH sensor
2017-12-20 DHT notes
2017-12-20 debug DHT sensor
2017-12-20 debug audio switches
2017-12-25 some debugging
2017-12-28 add pixel cleanup and dim
2017-12-28 cleanup and debug
2017-12-28 fix link tx audio
2017-12-28 add command line options, xmlconfig write and verbosity and debug
2017-12-29 debug link1 audio
2017-12-29 threading debug and cleanup
2017-12-29 initial cut at setup script
2017-12-29 more documentation
2017-12-29 debug OK messge
2017-12-29 add debug code
2017-12-29 Differentiate 456 and 789 commands
2017-12-31 link 1 up and down debugging
2017-12-31 try removing usbhid
2017-12-31 syntax error
2017-12-31 second attempt to disabl;e usbhid
2017-12-31 fix link clearing
2018-01-04 clean up and debug of port detect
2018-01-04 some cleanup of portDetect
2018-01-04 more sound card robustness
2018-01-06 more init options and more robustness
2018-01-06 clean up port detcion errors
2018-01-06 improve messaging
2018-02-04 gpio tester
2018-02-06 test in python3
2018-02-09 set spi speed for ADC to under 3.6Mhz
2018-02-09 adjust spi timing
2018-07-02 auto start script
2018-08-18 Switched to espeak-ng and new vioce
2020-01-05 added pl board control
2020-02-09 tx and kenwood control
2020-02-09 I2C 0 testing
2020-02-16 update kenwood tuning gui
2020-02-17 more kenwood tuning and espeak notes
2020-02-21 start adding link port control
2020-02-25 working on linking code
2020-02-25 correct a few typos
2023-02-26 add notes
2023-12-31 updated for newer versions
2024-01-02 setup
2024-01-02 bookworm updates
2024-03-08 python cleanup for newer python
2024-03-10 link setup in gui
2024-03-12 more gui functionality
2024-03-12 more debug of gui
2024-03-18 more port gui
2024-03-18 utility functions
2024-03-19 add number of cores
2024-06-01 syntax
